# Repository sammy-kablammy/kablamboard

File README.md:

# keyboards

## kablamboard

a 36 key "unibody split" column-staggered ergonomic keyboard

includes a rotary encoder (for funsies!)

based on the RP2040 zero because it's cheap

inspired by
[reviung41](https://github.com/gtips/reviung),
[corne](https://github.com/foostan/crkbd),
[splaytoraid](https://github.com/freya-irl/splaytoraid40),
and [cheapino](https://github.com/tompi/cheapino)

(see *kablamboard* branch)

## kablampad

a 4x3 macropad

my first pcb project

## firmware?

the firmware for all of my keyboards is over in
[my QMK fork](https://github.com/sammy-kablammy/qmk_firmware)

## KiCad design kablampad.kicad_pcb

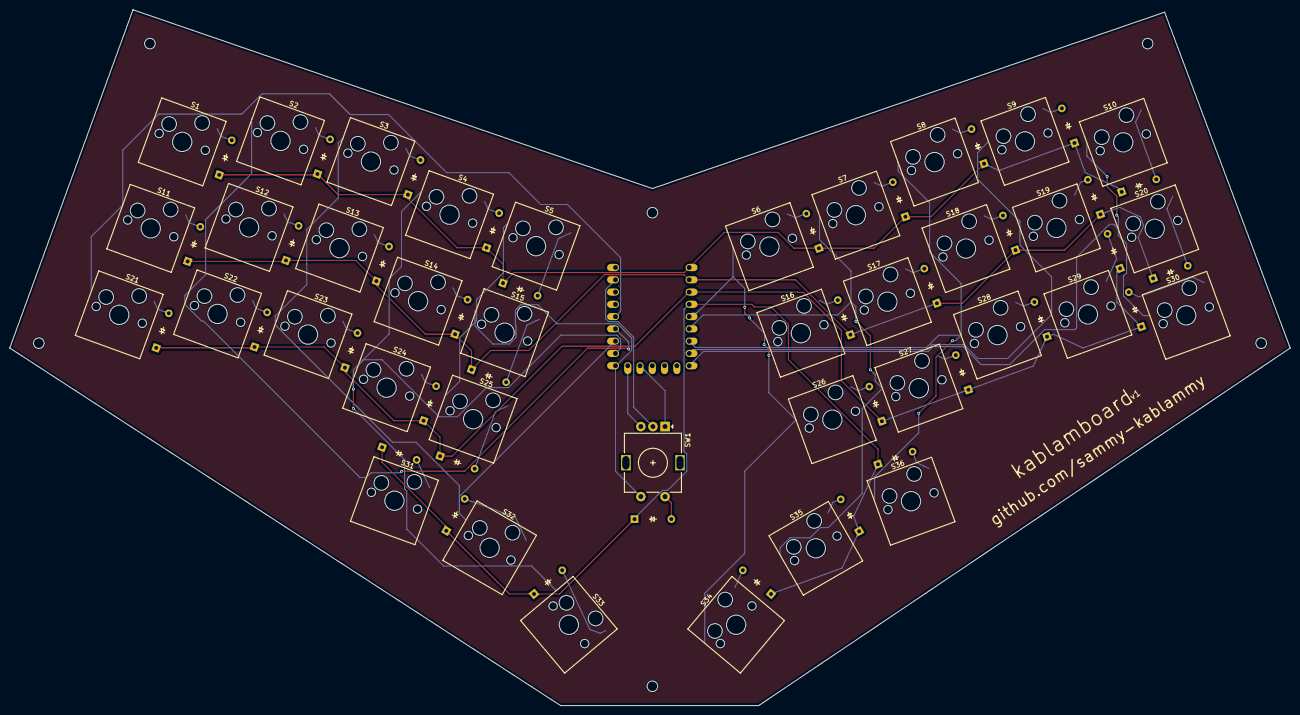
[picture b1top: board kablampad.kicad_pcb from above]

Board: 2 copper layers, 265.0 x 144.0 mm, 75 parts (0 on the bottom side), 54 nets.

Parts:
D1, D2, D3, D4, D5, D6, D7, D8, D9, D10, D11, D12, D13, D14, D15, D16, D17, D18, D19, D20, D21, D22, D23, D24, D25, D26, D27, D28, D29, D30, D31, D32, D33, D34, D35, D36, D37: Diode; Diode_DO-35
S1, S2, S3, S4, S5, S6, S7, S8, S9, S10, S11, S12, S13, S14, S15, S16, S17, S18, S19, S20, S21, S22, S23, S24, S25, S26, S27, S28, S29, S30, S31, S32, S33, S34, S35, S36: Keyswitch; Hotswap_MX_1.00u
SW1: RotaryEncoder_Switch; RotaryEncoder_Alps_EC11E-Switch_Vertical_H20mm
U1: RP2040_Zero

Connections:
/Column 0: S1.1, S11.1, S21.1, U1.19 (28)
/Column 1: S2.1, S12.1, S22.1, S31.1, U1.18 (27)
/Column 2: S3.1, S13.1, S23.1, S32.1, U1.17 (26)
/Column 3: S4.1, S14.1, S24.1, S33.1, U1.16 (15)
/Column 4: S5.1, S15.1, S25.1, SW1.S1, U1.15 (14)
/Column 5: S6.1, S16.1, S26.1, S34.1, U1.5 (4)
/Column 6: S7.1, S17.1, S27.1, S35.1, U1.6 (5)
/Column 7: S8.1, S18.1, S28.1, S36.1, U1.7 (6)
/Column 8: S9.1, S19.1, S29.1, U1.8 (7)
/Column 9: S10.1, S20.1, S30.1, U1.9 (8)
/Encoder A: SW1.A, U1.13 (12)
/Encoder B: SW1.B, U1.14 (13)
/Encoder C: SW1.C, U1.22 (GND)
/Row 0: D1.1 (K), D2.1 (K), D3.1 (K), D4.1 (K), D5.1 (K), D6.1 (K), D7.1 (K), D8.1 (K), D9.1 (K), D10.1 (K), U1.1 (0)
/Row 1: D11.1 (K), D12.1 (K), D13.1 (K), D14.1 (K), D15.1 (K), D16.1 (K), D17.1 (K), D18.1 (K), D19.1 (K), D20.1 (K), U1.2 (1)
/Row 2: D21.1 (K), D22.1 (K), D23.1 (K), D24.1 (K), D25.1 (K), D26.1 (K), D27.1 (K), D28.1 (K), D29.1 (K), D30.1 (K), U1.3 (2)
/Row 3: D31.1 (K), D32.1 (K), D33.1 (K), D34.1 (K), D35.1 (K), D36.1 (K), D37.1 (K), U1.4 (3)
unnamed: D1.2 (A), S1.2
unnamed: D2.2 (A), S2.2
unnamed: D3.2 (A), S3.2
unnamed: D4.2 (A), S4.2
unnamed: D5.2 (A), S5.2
unnamed: D6.2 (A), S6.2
unnamed: D7.2 (A), S7.2
unnamed: D8.2 (A), S8.2
unnamed: D9.2 (A), S9.2
unnamed: D10.2 (A), S10.2
unnamed: D11.2 (A), S11.2
unnamed: D12.2 (A), S12.2
unnamed: D13.2 (A), S13.2
unnamed: D14.2 (A), S14.2
unnamed: D15.2 (A), S15.2
unnamed: D16.2 (A), S16.2
unnamed: D17.2 (A), S17.2
unnamed: D18.2 (A), S18.2
unnamed: D19.2 (A), S19.2
unnamed: D20.2 (A), S20.2
unnamed: D21.2 (A), S21.2
unnamed: D22.2 (A), S22.2
unnamed: D23.2 (A), S23.2
unnamed: D24.2 (A), S24.2
unnamed: D25.2 (A), S25.2
unnamed: D26.2 (A), S26.2
unnamed: D27.2 (A), S27.2
unnamed: D28.2 (A), S28.2
unnamed: D29.2 (A), S29.2
unnamed: D30.2 (A), S30.2
unnamed: D31.2 (A), S31.2
unnamed: D32.2 (A), S32.2
unnamed: D33.2 (A), S33.2
unnamed: D34.2 (A), S34.2
unnamed: D35.2 (A), S35.2
unnamed: D36.2 (A), S36.2
unnamed: D37.2 (A), SW1.S2

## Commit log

2024-07-07 initial creation of kablampad v0.1
2024-09-18 made kablamboard v1, idk how i'm gonna merge later (but that's a future problem, yaknow?)
2024-10-12 add images
